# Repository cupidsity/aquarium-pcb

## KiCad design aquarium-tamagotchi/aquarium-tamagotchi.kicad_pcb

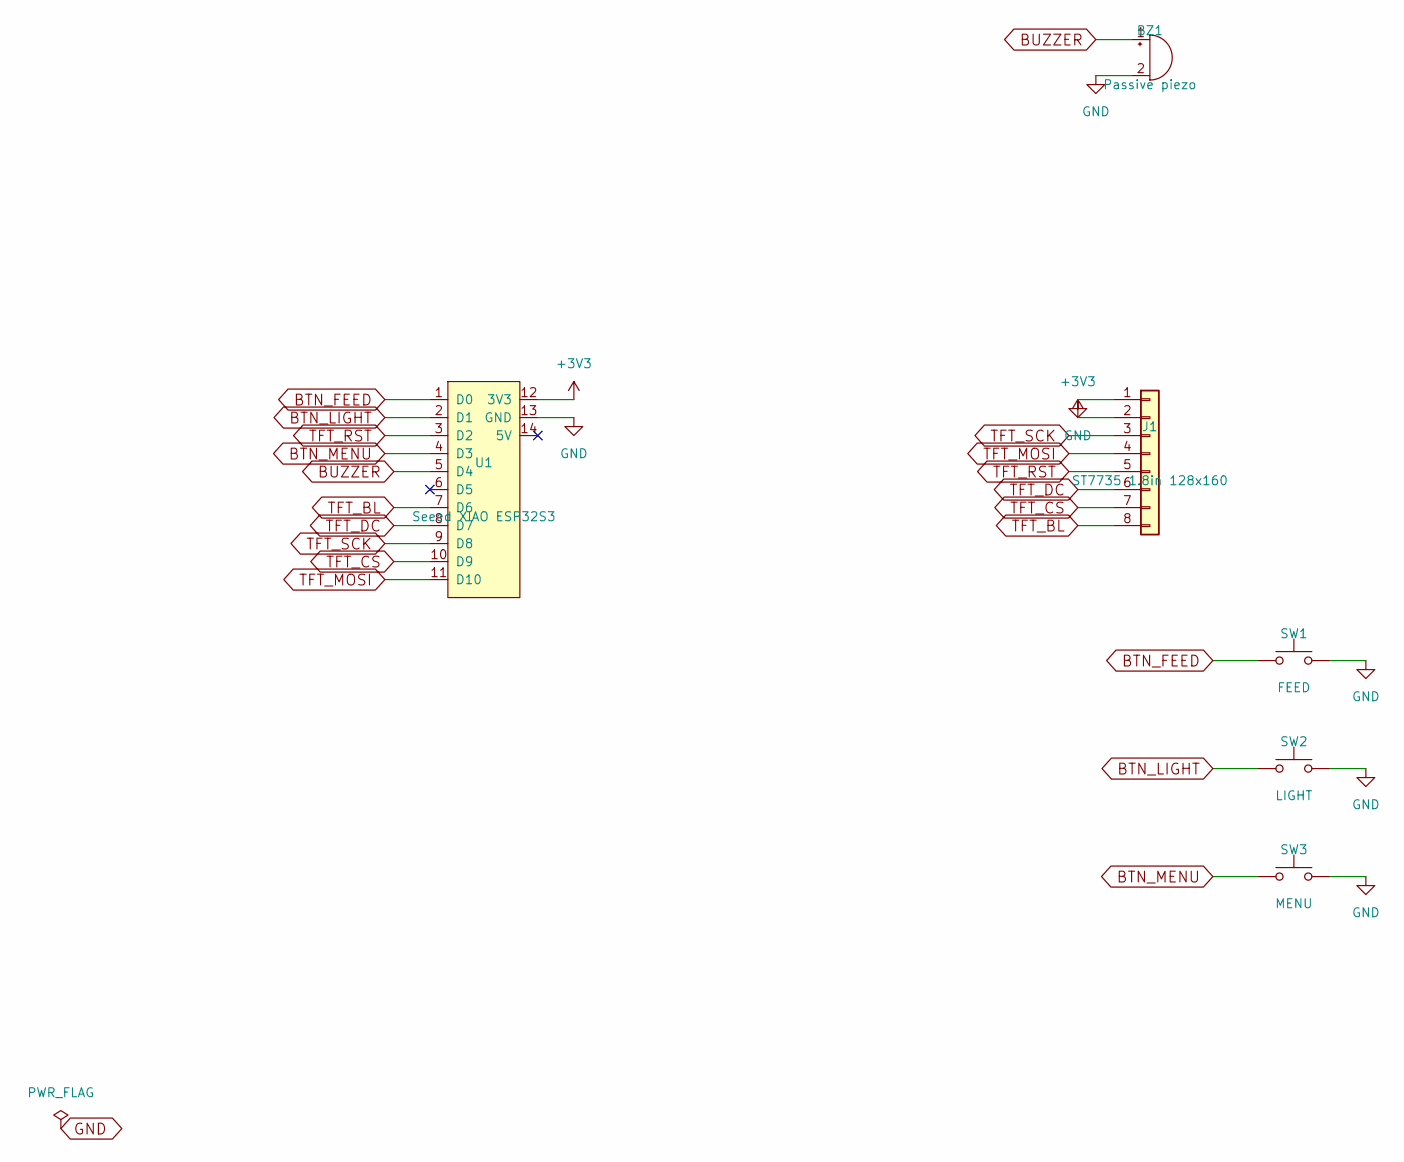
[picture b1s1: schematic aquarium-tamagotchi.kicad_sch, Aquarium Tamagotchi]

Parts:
BZ1: Passive piezo; Buzzer_12x9.5RM7.6
J1: ST7735 1.8in 128x160; PinSocket_1x08_P2.54mm_Vertical
SW1: FEED; SW_PUSH_6mm
SW2: LIGHT; SW_PUSH_6mm
SW3: MENU; SW_PUSH_6mm
U1: Seeed XIAO ESP32S3; XIAO_ESP32S3_THT

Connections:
+3V3: J1.2, U1.12 (3V3)
BTN_FEED: SW1.1, U1.1 (D0)
BTN_LIGHT: SW2.1, U1.2 (D1)
BTN_MENU: SW3.1, U1.4 (D3)
BUZZER: BZ1.1 (+), U1.5 (D4)
GND: BZ1.2 (-), J1.1, SW1.2, SW2.2, SW3.2, U1.13 (GND)
TFT_BL: J1.8, U1.7 (D6)
TFT_CS: J1.7, U1.10 (D9)
TFT_DC: J1.6, U1.8 (D7)
TFT_MOSI: J1.4, U1.11 (D10)
TFT_RST: J1.5, U1.3 (D2)
TFT_SCK: J1.3, U1.9 (D8)

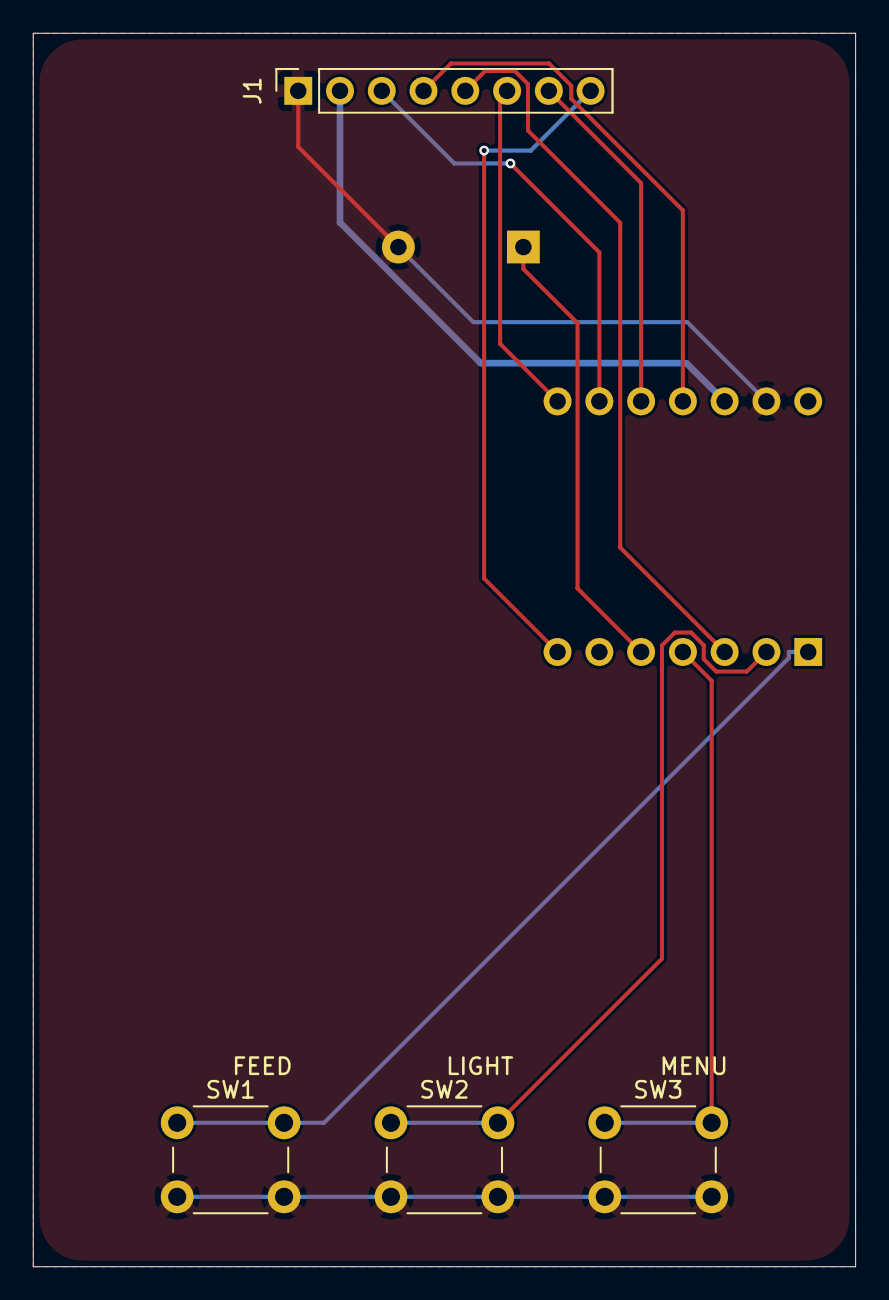
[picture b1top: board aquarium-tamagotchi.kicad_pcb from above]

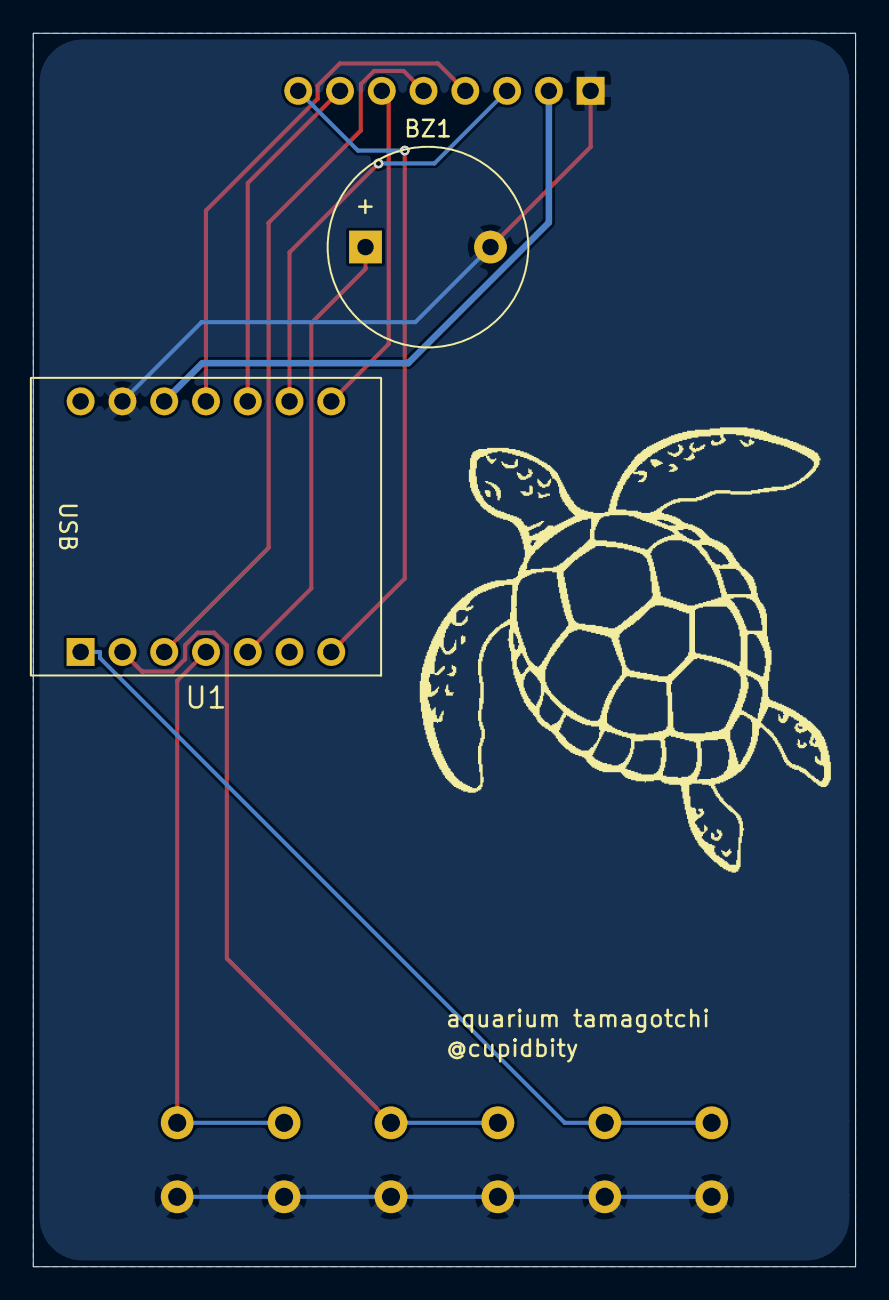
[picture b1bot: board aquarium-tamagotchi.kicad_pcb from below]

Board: 2 copper layers, 50.0 x 75.0 mm, 6 parts (2 on the bottom side), 12 nets.
